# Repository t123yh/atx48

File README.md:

# ATX48: 48V DC-ATX Power Supply

An isolated 44V-70V to ATX power supply. Built for DC UPS systems for your home datacenter.

## Structure

## Features

### Hot Plug with Soft Start

LM5067 hot swap controller is used to limit inrush current, eliminating any sparks on hot-plug. It also limits input current to 10A, protecting over-current situations.

### High efficiency conversion

[Huawei GDQ33S12B/P](https://www.huaweipowersolutions.com/GDQ33S12B(P).pdf) is used as the main converter. It provides 12V/33A output with up to 96.0% efficiency.

For 3.3V and 5V, three ZXDN10 modules are used (3.3V motherboard, 5V motherboard, 5V HDD), with up to 94% efficiency (See [testing](https://blog.iccfish.com/2021/08/02/%E7%9B%98%E4%B8%80%E4%B8%8B%E6%9C%80%E8%BF%91%E6%94%B6%E5%88%B0%E7%9A%84%E4%BA%8C%E6%89%8Bdc%E9%9D%9E%E9%9A%94%E7%A6%BB%E9%99%8D%E5%8E%8B%E6%A8%A1%E5%9D%97/)).

5VSB voltage is provided by an AV10-48S05 module, with up to 10W standby power output. The main converter is disabled in standby mode to avoid unnecessary energy waste when PC is off.

This power supply does not provide -12V and -5V output, because no motherboards use them today.

### Fully isolated
Input and output are fully isolated. Works within either +48V or -48V setup.

### LED indicators

Built with 8 LED indicators to monitor input and output status (see photos below).

### ATX installation

Installs to any chassis with ATX power slot.

## Connectors

### Input

An XT60PB-M connector is present on board. Use any XT60 compatible connector as power input.

### Output

This power supply provides the following power outputs:

* 1 \* ATX 24-Pin
* 2 \* 8-Pin 12V for CPU and PCIe
* 2 \* 4-Pin for SATA

For 24-Pin ATX power output, use a 24P to 24P cable with identical pinouts.

For SATA HDD/SDD power output, use Lenovo 4-Pin to SATA connector, such as [this](https://www.amazon.com/Genuine-Lenovo-7-5mm-Power-54Y8286/dp/B07DL9P1V7).

For PCIe / CPU 8-Pin power, use 12V modular cables for Seasonic FOCUS+/KM3/XP2/XM2/XP3 series.
 
## Photos

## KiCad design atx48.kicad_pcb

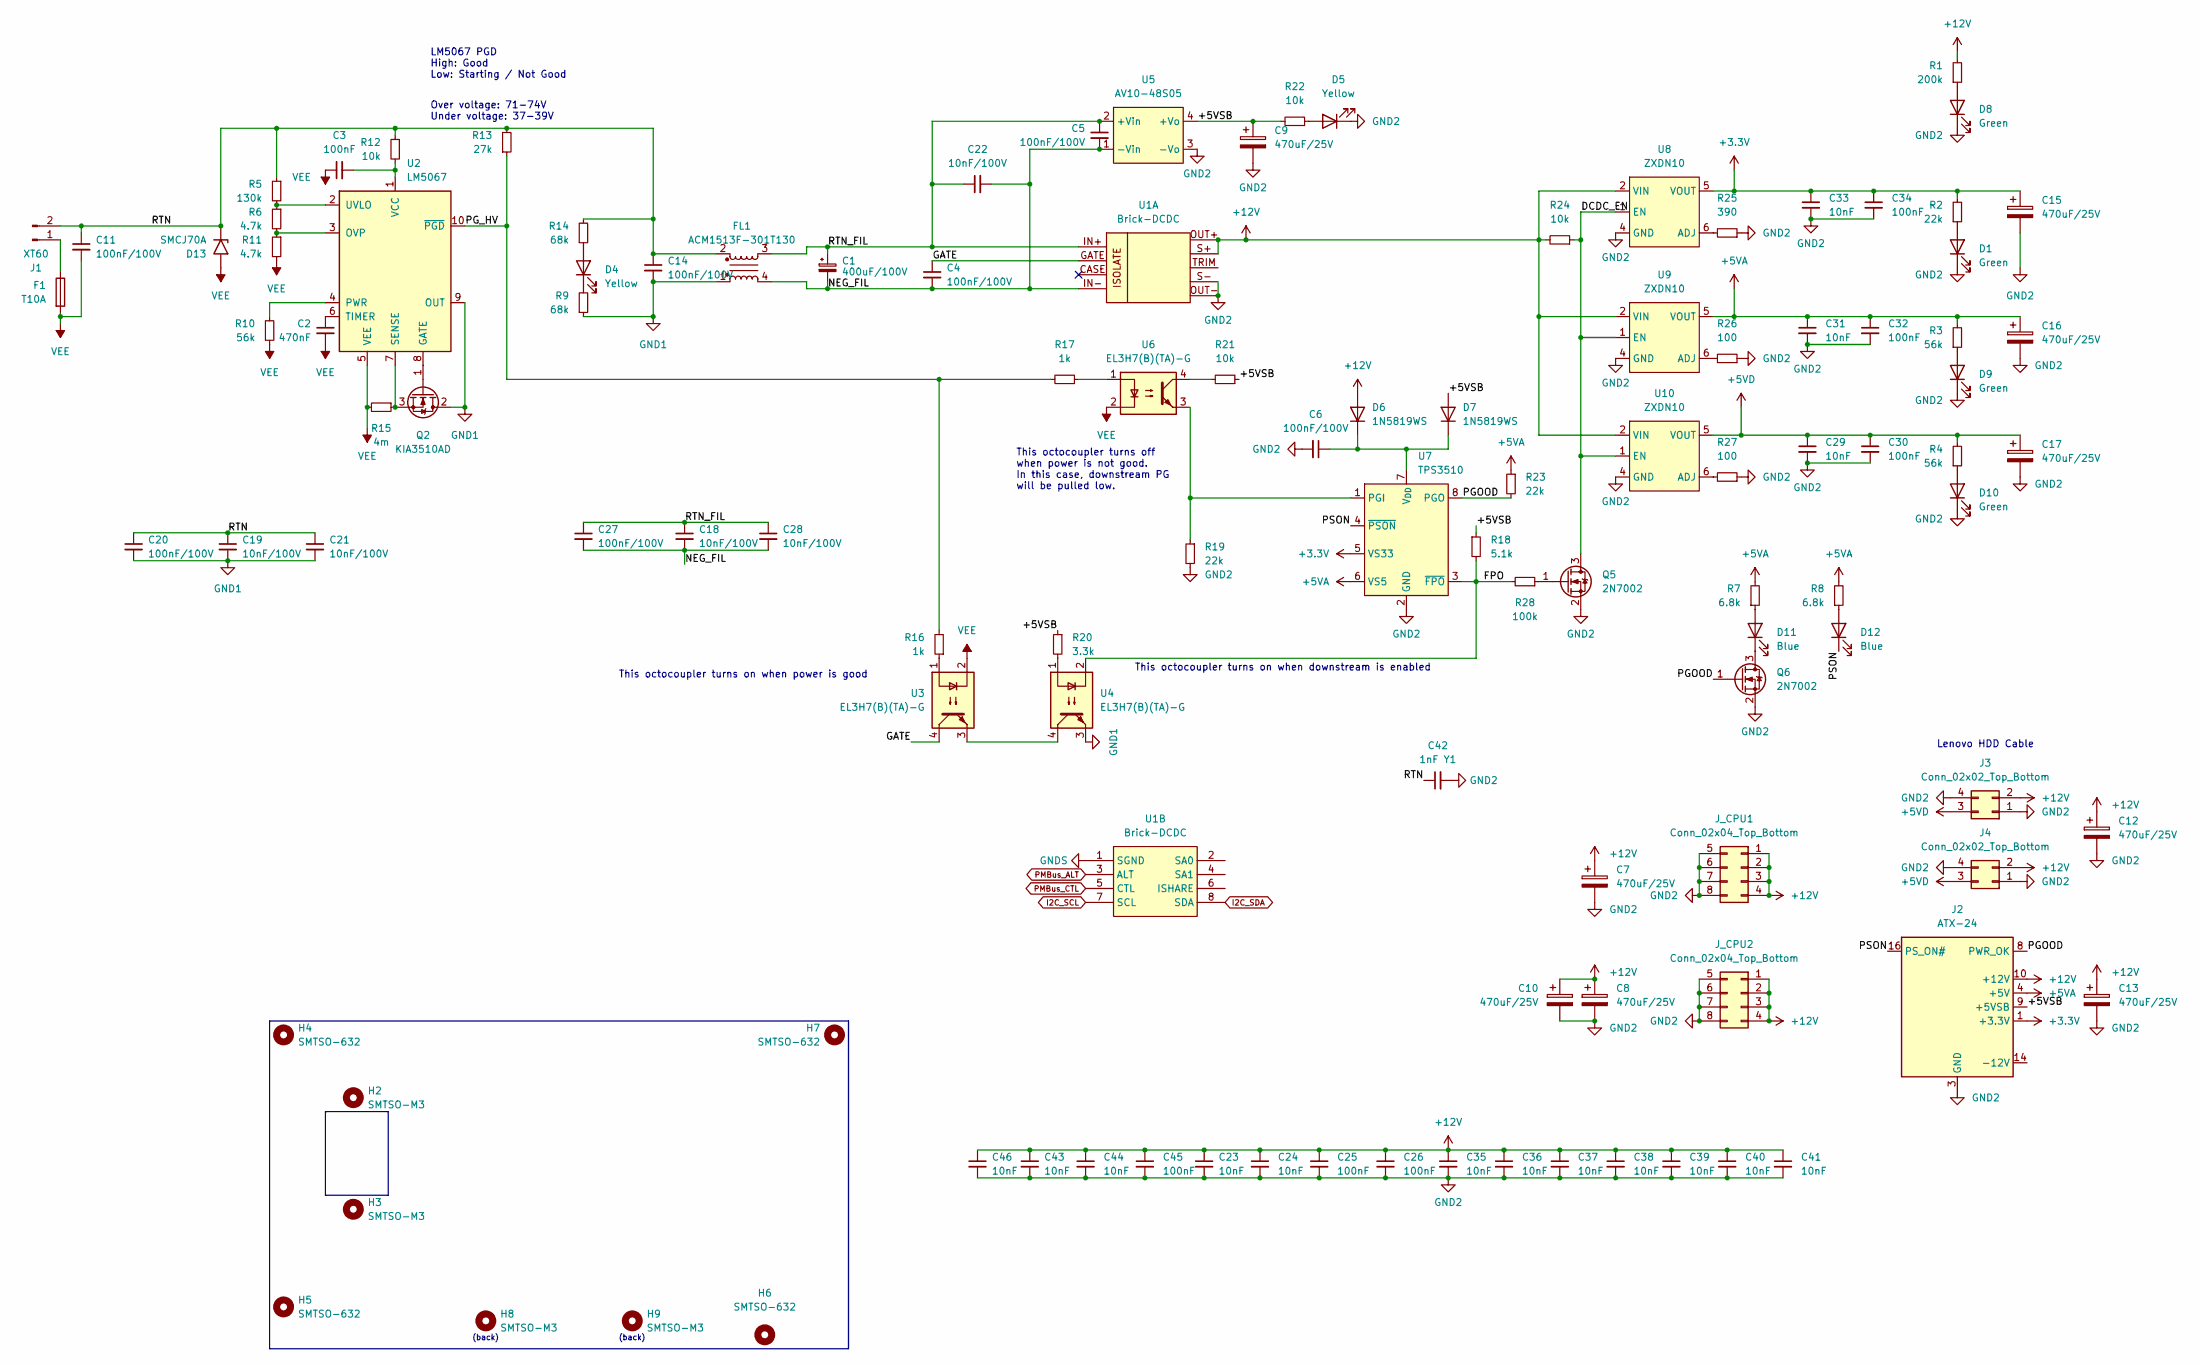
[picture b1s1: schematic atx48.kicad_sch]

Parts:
C1: 400uF/100V; C_Disc_D5.0mm_W2.5mm_P5.00mm
C2: 470nF; 0402_C
C3, C25, C26, C30, C32, C34, C45: 100nF; 0805_C
C4, C5, C6, C11, C14, C20, C27: 100nF/100V; 0805_C
C7, C8, C9, C10, C12, C13, C15, C16, C17: 470uF/25V; CP_Radial_D6.3mm_P2.50mm
C18, C19, C21, C22, C28: 10nF/100V; 0603_C
C23, C24, C29, C31, C33, C35, C36, C37, C38, C39, C40, C41, C43, C44, C46: 10nF; 0603_C
C42: 1nF Y1; C_Disc_D8.0mm_W5.0mm_P10.00mm
D1, D8, D9, D10: Green; 0603_LED_S1_NUM
D4, D5: Yellow; 0603_LED_S1_NUM
D6, D7: 1N5819WS; SOD-323
D11, D12: Blue; 0603_LED_S1_NUM
D13: SMCJ70A; D_SMC
F1: T10A; Fuse_1812_4532Metric
FL1: ACM1513F-301T130; ACM1513
H2, H3, H8, H9: SMTSO-M3; MountingHole_SMTSO-M3
H4, H5, H6, H7: SMTSO-632; MountingHole_SMTSO-632
J1: XT60; AMASS_XT60-M_1x02_P7.20mm_Vertical
J2: ATX-24; ATX-24P
J3, J4: Conn_02x02_Top_Bottom; ATX-4P
J_CPU1, J_CPU2: Conn_02x04_Top_Bottom; ATX-8P-Square
Q2: KIA3510AD; TO-252-2
Q5, Q6: 2N7002; SOT-23
R1: 200k; 0402_R
R2, R19, R23: 22k; 0402_R
R3, R4, R10: 56k; 0402_R
R5: 130k; 0603_R
R6, R11: 4.7k; 0402_R
R7, R8: 6.8k; 0402_R
R9, R14: 68k; 0603_R
R12: 10k; 1206_R
R13: 27k; 0805_R
R15: 4m; 2512_R
R16, R17: 1k; 0603_R
R18: 5.1k; 0402_R
R20: 3.3k; 0402_R
R21, R22: 10k; 0402_R
R24: 10k; 0603_R
R25: 390; 0603_R
R26, R27: 100; 0402_R
R28: 100k; 0402_R
U1: Brick-DCDC; Quarter-Brick-PMBus
U2: LM5067; MSOP-10_3x3mm_P0.5mm
U3, U4, U6: EL3H7(B)(TA)-G; SOP-4_4.4x2.6mm_P1.27mm
U5: AV10-48S05; AV10-48Sxx
U7: TPS3510; SOIC-8_3.9x4.9mm_P1.27mm
U8, U9, U10: ZXDN10

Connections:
+3.3V: C15.1, C33.1, C34.1, J2.1 (+3.3V), J2.2 (+3.3V), J2.12 (+3.3V), J2.13 (+3.3V), R2.2, U7.5 (VS33), U8.5 (VOUT)
+5VA: C16.1, C31.1, C32.1, J2.4 (+5V), J2.6 (+5V), J2.21 (+5V), J2.22 (+5V), J2.23 (+5V), R3.2, R7.2, R8.2, R23.1, U7.6 (VS5), U9.5 (VOUT)
+5VD: C17.1, C29.1, C30.1, J3.3, J4.3, R4.2, U10.5 (VOUT)
+12V: C7.1, C8.1, C10.1, C12.1, C13.1, C23.1, C24.1, C25.1, C26.1, C35.1, C36.1, C37.1, C38.1, C39.1, C40.1, C41.1, C43.1, C44.1, C45.1, C46.1, D6.2 (A), J2.10 (+12V), J2.11 (+12V), J3.2, J4.2, J_CPU1.1, J_CPU1.2, J_CPU1.3, J_CPU1.4, J_CPU2.1, J_CPU2.2, J_CPU2.3, J_CPU2.4, R1.2, R24.2, U1.OUT+, U1.S+, U8.2 (VIN), U9.2 (VIN), U10.2 (VIN)
/+5VSB: C9.1, D7.2 (A), J2.9 (+5VSB), R18.1, R20.1, R21.1, R22.2, U5.4 (+Vo)
/DCDC_EN: Q5.3 (D), R24.1, U8.1 (EN), U9.1 (EN), U10.1 (EN)
/FPO: R18.2, R28.2, U4.2, U7.3 (~FPO)
/GATE: C4.1, U1.GATE, U3.4
/NEG_FIL: C1.2, C4.2, C5.2, C18.2, C22.2, C27.2, C28.2, FL1.4, U1.IN-, U5.1 (-Vin)
/PGOOD: J2.8 (PWR_OK), Q6.1 (G), R23.2, U7.8 (PGO)
/PG_HV: R13.1, R16.2, R17.2, U2.10 (~PGD)
/PSON: D12.1 (K), J2.16 (PS_ON#), U7.4 (~PSON)
/RTN: C11.1, C14.1, C19.1, C20.1, C21.1, C42.1, D13.1 (A1), FL1.2, J1.2, R5.1, R12.1, R13.2, R14.2
/RTN_FIL: C1.1, C5.1, C18.1, C22.1, C27.1, C28.1, FL1.3, U1.IN+, U5.2 (+Vin)
GND1: C14.2, C19.2, C20.2, C21.2, FL1.1, Q2.2 (D), R9.1, U2.9 (OUT), U4.3
GND2: C6.2, C7.2, C8.2, C9.2, C10.2, C12.2, C13.2, C15.2, C16.2, C17.2, C23.2, C24.2, C25.2, C26.2, C29.2, C30.2, C31.2, C32.2, C33.2, C34.2, C35.2, C36.2, C37.2, C38.2, C39.2, C40.2, C41.2, C42.2, C43.2, C44.2, C45.2, C46.2, D1.1 (K), D5.1 (K), D8.1 (K), D9.1 (K), D10.1 (K), J2.3 (GND), J2.5 (GND), J2.7 (GND), J2.15 (GND), J2.17 (GND), J2.18 (GND), J2.19 (GND), J2.24 (GND), J3.1, J3.4, J4.1, J4.4, J_CPU1.5, J_CPU1.6, J_CPU1.7, J_CPU1.8, J_CPU2.5, J_CPU2.6, J_CPU2.7, J_CPU2.8, Q5.2 (S), Q6.2 (S), R19.2, R25.1, R26.1, R27.1, U1.OUT-, U1.S-, U5.3 (-Vo), U7.2 (GND), U8.3 (GND), U8.4 (GND), U9.3 (GND), U9.4 (GND), U10.3 (GND), U10.4 (GND)
GNDS: U1.1 (SGND)
I2C_SCL: U1.7 (SCL)
I2C_SDA: U1.8 (SDA)
unnamed: D1.2 (A), R2.1
unnamed: D4.2 (A), R14.1
unnamed: D4.1 (K), R9.2
unnamed: D5.2 (A), R22.1
unnamed: C6.1, D6.1 (K), D7.1 (K), U7.7 (V_{DD})
unnamed: D8.2 (A), R1.1
unnamed: D9.2 (A), R3.1
unnamed: D10.2 (A), R4.1
unnamed: D11.2 (A), R7.1
unnamed: D11.1 (K), Q6.3 (D)
unnamed: D12.2 (A), R8.1
unnamed: F1.1, J1.1
unnamed: Q2.1 (G), U2.8 (GATE)
unnamed: Q2.3 (S), R15.1, U2.7 (SENSE)
unnamed: Q5.1 (G), R28.1
unnamed: R16.1, U3.1
unnamed: R17.1, U6.1
unnamed: R20.2, U4.1
unnamed: R21.2, U6.4
unnamed: R6.2, R11.1, U2.3 (OVP)
unnamed: R10.2, U2.4 (PWR)
unnamed: C2.1, U2.6 (TIMER)
unnamed: R5.2, R6.1, U2.2 (UVLO)
unnamed: C3.2, R12.2, U2.1 (VCC)
unnamed: U3.3, U4.4
unnamed: R19.1, U6.3, U7.1 (PGI)
unnamed: R25.2, U8.6 (ADJ)
unnamed: R26.2, U9.6 (ADJ)
unnamed: R27.2, U10.6 (ADJ)
PMBus_ALT: U1.3 (ALT)
PMBus_CTL: U1.5 (CTL)
VEE: C2.2, C3.1, C11.2, D13.2 (A2), F1.2, R10.1, R11.2, R15.2, U2.5 (VEE), U3.2, U6.2

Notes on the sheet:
Over voltage: 71-74V Under voltage: 37-39V
This octocoupler turns off when power is not good. In this case, downstream PG will be pulled low.
This octocoupler turns on when downstream is enabled
Lenovo HDD Cable
(back)
LM5067 PGD High: Good Low: Starting / Not Good
This octocoupler turns on when power is good

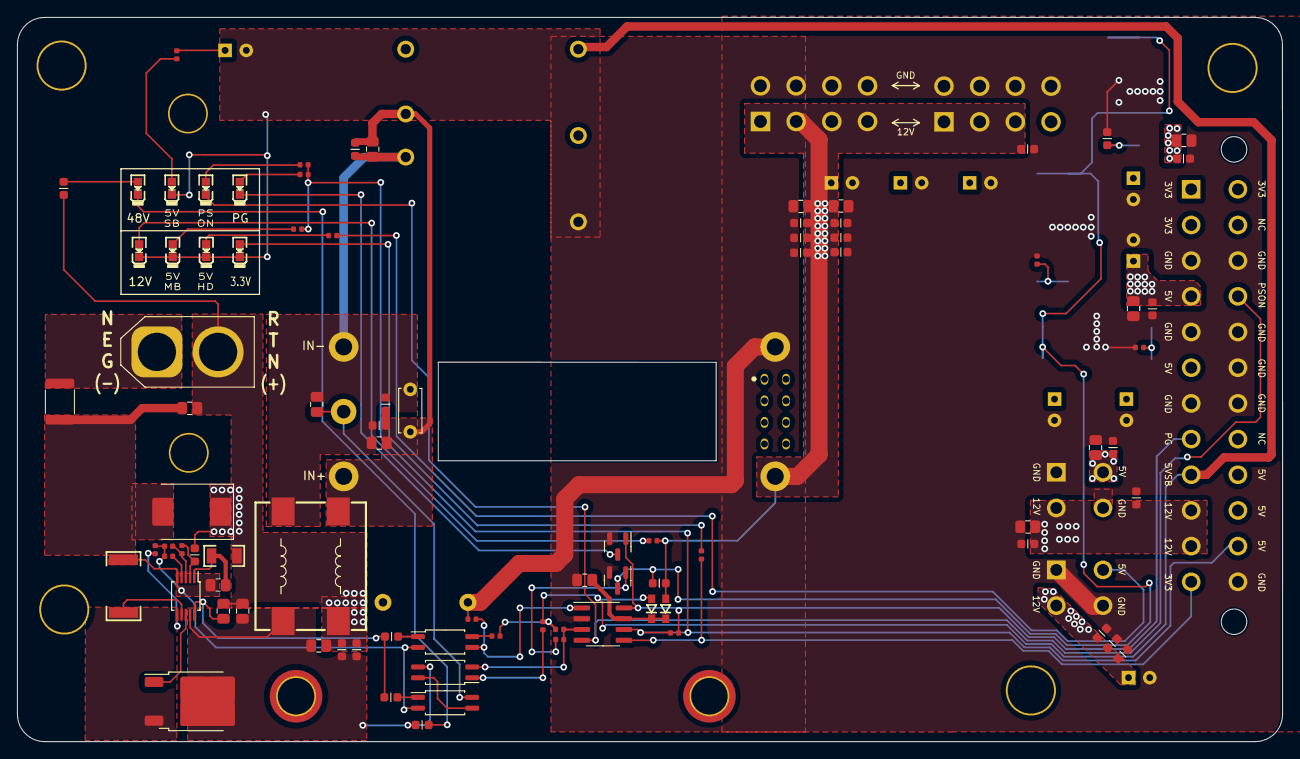
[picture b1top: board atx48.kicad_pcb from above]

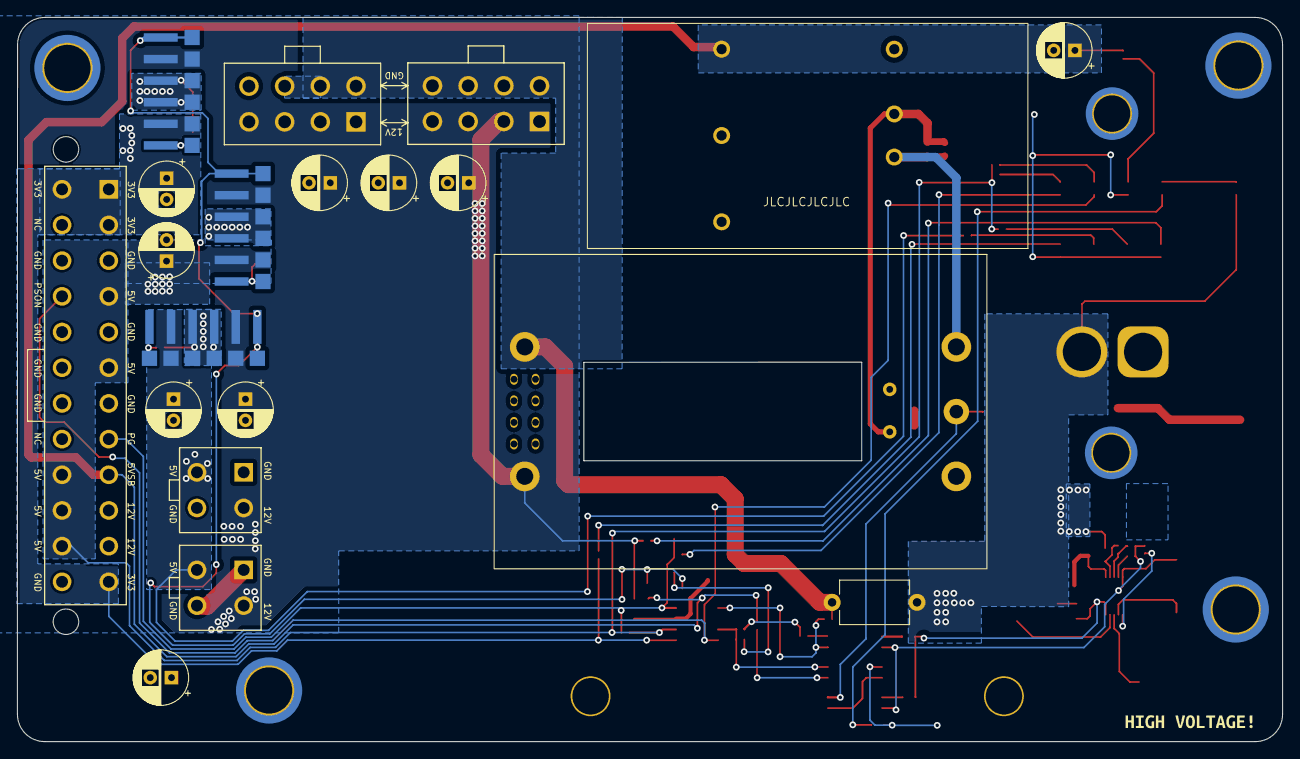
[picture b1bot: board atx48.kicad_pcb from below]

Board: 2 copper layers, 148.9 x 85.2 mm, 115 parts (26 on the bottom side), 46 nets.

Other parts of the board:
kibuzzard-62760563: G***; kibuzzard-62760563

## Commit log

2022-05-07 pmbus and normal
2022-05-07 change fuse footprint
2022-10-15 Temp
2022-10-17 change mounting hole
2022-10-18 TPS2350
2022-10-18 LM5067
2022-10-18 Layout improvements
2022-10-26 Adjust low voltage copper pour
2022-10-26 Adjust screw hole position
2022-10-26 Reduce LED brightness
2022-11-05 Revert "Adjust screw hole position"
    This reverts commit 63cac71901258e286d442f6c161a0cf4eb18ce6f.
2022-11-05 Add readme
2022-11-05 Rename
2022-11-06 Update img
2022-11-09 Enhance grouding
2022-11-09 Add photos and README
2024-01-18 Add filter capacitors; add Y cap
